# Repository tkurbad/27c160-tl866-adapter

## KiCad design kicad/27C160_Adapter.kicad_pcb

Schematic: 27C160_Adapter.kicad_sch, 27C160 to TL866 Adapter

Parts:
Q1: BC807; SOT-23
R1, R2, R3, R4, R5: 10k; R_0805_2012Metric
SW1: MS22D16
SW2: DIP; SW_DIP_SPSTx03_Slide_9.78x9.8mm_W7.62mm_P2.54mm
U1: 27C4002
ZX1: 3M_248-3345

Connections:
/A0: U1.21 (A0), ZX1.13
/A1: U1.22 (A1), ZX1.12
/A2: U1.23 (A2), ZX1.11
/A3: U1.24 (A3), ZX1.10
/A4: U1.25 (A4), ZX1.9
/A5: U1.26 (A5), ZX1.8
/A6: U1.27 (A6), ZX1.7
/A7: U1.28 (A7), ZX1.6
/A8: U1.29 (A8), ZX1.44
/A9: U1.31 (A9), ZX1.43
/A10: U1.32 (A10), ZX1.42
/A11: U1.33 (A11), ZX1.41
/A12: U1.34 (A12), ZX1.40
/A13: U1.35 (A13), ZX1.39
/A14: U1.36 (A14), ZX1.38
/A15: U1.37 (A15), ZX1.37
/A16: U1.38 (A16), ZX1.36
/A17: U1.39 (A17), ZX1.5
/A18: R3.1, SW2.3, ZX1.4
/A19: R2.1, SW2.2, ZX1.45
/A20: R1.1, SW1.3 (S), SW2.1
/D0: U1.19 (D0), ZX1.17
/D1: U1.18 (D1), ZX1.19
/D2: U1.17 (D2), ZX1.21
/D3: U1.16 (D3), ZX1.23
/D4: U1.15 (D4), ZX1.26
/D5: U1.14 (D5), ZX1.28
/D6: U1.13 (D6), ZX1.30
/D7: U1.12 (D7), ZX1.32
/D8: U1.10 (D8), ZX1.18
/D9: U1.9 (D9), ZX1.20
/D10: U1.8 (D10), ZX1.22
/D11: U1.7 (D11), ZX1.24
/D12: U1.6 (D12), ZX1.27
/D13: U1.5 (D13), ZX1.29
/D14: U1.4 (D14), ZX1.31
/D15: U1.3 (D15), ZX1.33
/E: U1.2 (/CE), ZX1.14
/N$1: Q1.1 (B), R5.2
/N$2: SW1.2, ZX1.35
/N$4: Q1.3 (C), R4.2, SW1.6 (S1)
/N$5: SW1.4 (O1), U1.20 (/G)
/N$6: SW1.5 (P1), ZX1.16
/VPP: Q1.2 (E), SW1.1 (O), U1.1 (VPP)
GND: R4.1, SW2.4, SW2.5, SW2.6, U1.11 (GND), U1.30 (GND), ZX1.15, ZX1.34
VCC: R1.2, R2.2, R3.2, R5.1, U1.40 (VCC), ZX1.25

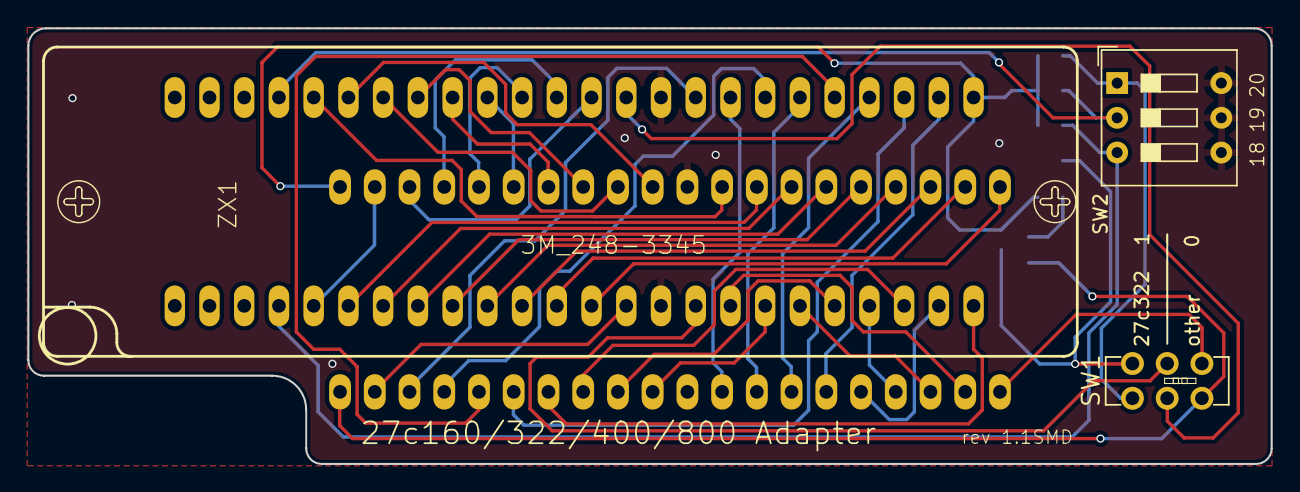
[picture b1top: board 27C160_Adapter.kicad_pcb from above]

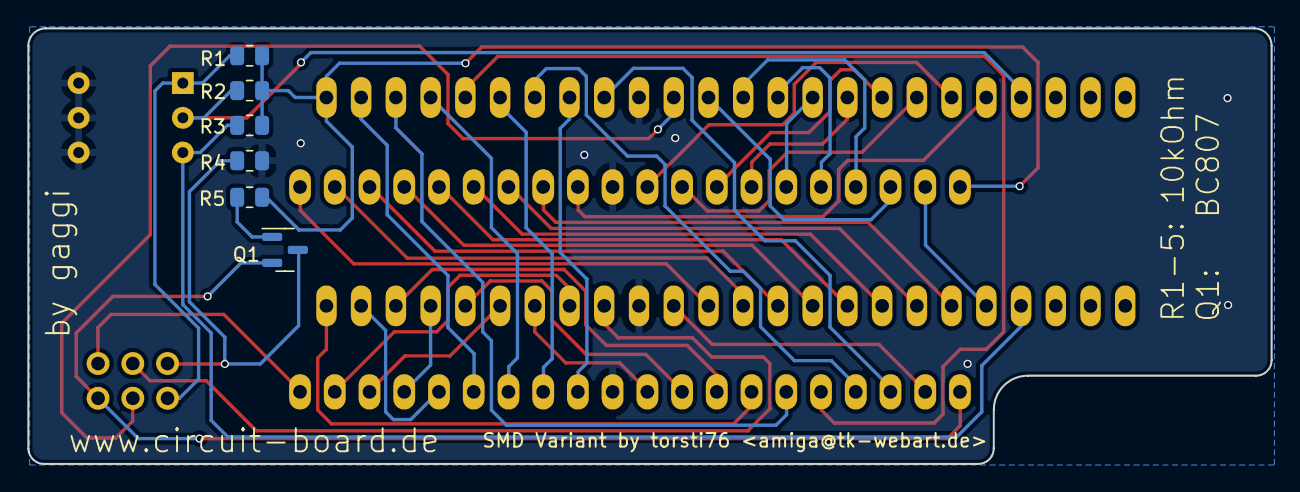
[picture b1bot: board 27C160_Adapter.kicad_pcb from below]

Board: 2 copper layers, 90.9 x 31.9 mm, 10 parts (6 on the bottom side), 46 nets.

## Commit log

2022-01-31 Cleanup
2022-01-31 Shrunk PCB size Converted resistors and transistor to SMD Introduced GND fills Converted to Kicad 5.x
2022-01-31 Updated gerbers
2022-01-31 Added rendered image
2022-02-11 Refinements / Upgrade to KiCAD 6
2022-05-03 Removed obsolete image

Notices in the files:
kicad/27C160_Adapter.kicad_pcb:
License: GPLv3 License:  GPLv3 (s. license.txt)
© 2017 gaggi [https://github.com/gaggi/27c160-tl866-adapter]
